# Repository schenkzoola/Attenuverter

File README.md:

<picture>
  <source media="(prefers-color-scheme: dark)" srcset="docs/images/logo-light.png">
  
</picture>

# Attenuverter

A 6HP Eurorack quad attenuverter from **Schenktronics**. Each of its four channels scales a signal by anywhere from ×1, through zero, to ×−1 (inverted), with a click at zero. Every input is normalled to +5 V, so with nothing plugged in, each channel is a manual offset from −5 V to +5 V.

## Features

- 6HP Eurorack, 20 mm deep. 16 mA on +12 V and 9 mA on −12 V.
- Four channels, each turning a signal down, off, or upside down
- Center-detent knobs, so zero is easy to find by feel
- Inputs normalled to +5 V: four manual offset voltages when nothing's plugged in
- Reverse-power protection on both rails

## Documentation

| Document | For | PDF |
|----------|-----|-----|
| [User Manual](docs/manual.md) | Using the module | [PDF](docs/pdf/attenuverter-manual.pdf) |
| [Assembly Guide](docs/assembly-guide.md) | Building the kit | [PDF](docs/pdf/attenuverter-assembly-guide.pdf) |
| [Bill of Materials](docs/BOM.md) ([CSV](docs/BOM.csv)) | Parts and sourcing | |

## Repository layout

```
Attenuverter/                 Main PCB (KiCad 5.1)
  Attenuverter.sch              Schematic
  Attenuverter.kicad_pcb        PCB layout
  Attenuverter.step             3D model
  Gerbers/, *Gerbers.zip        Fabrication files
  attenuverter BOM.xlsx         Original BOM spreadsheet
AttenuverterFaceplate/        Faceplate (KiCad 5.1, made as an aluminium PCB)
  *.dxf                         Panel outline and drill drawing
  *Gerbers/, *Gerbers.zip       Fabrication files
docs/                         Manual, assembly guide, BOM, images
  drawings/                     Scripts that generate the drawings
  pdf/                          PDF versions and their build settings
```

## Fabrication

| Board | Size | Layers | Thickness | Notes |
|-------|------|--------|-----------|-------|
| Main PCB | 30 × 100 mm | 2 | 1.6 mm | Standard green is fine |
| Faceplate | 30 × 128.5 mm | 1 | 1.6 mm | Aluminium PCB, white solder mask, black silkscreen. Only the front copper layer is used, so FR4 works too. |

Upload the matching `*Gerbers.zip` to any common PCB fab.

## License

This hardware design and its documentation are licensed under [CC BY-NC-SA 4.0](https://creativecommons.org/licenses/by-nc-sa/4.0/). See [LICENSE](LICENSE).

The Schenktronics name and logo are trademarks of Nathan Schenk and are not covered by the CC BY-NC-SA 4.0 license.

## Links

- Tindie: <https://www.tindie.com/products/schenktronics/attenuverter/>
- ModularGrid: <https://modulargrid.net/e/schenktronics-attenuverter>
- Build video: <https://www.youtube.com/watch?v=QJxtZVHBpq0>
- Website: <https://schenktronics.com>

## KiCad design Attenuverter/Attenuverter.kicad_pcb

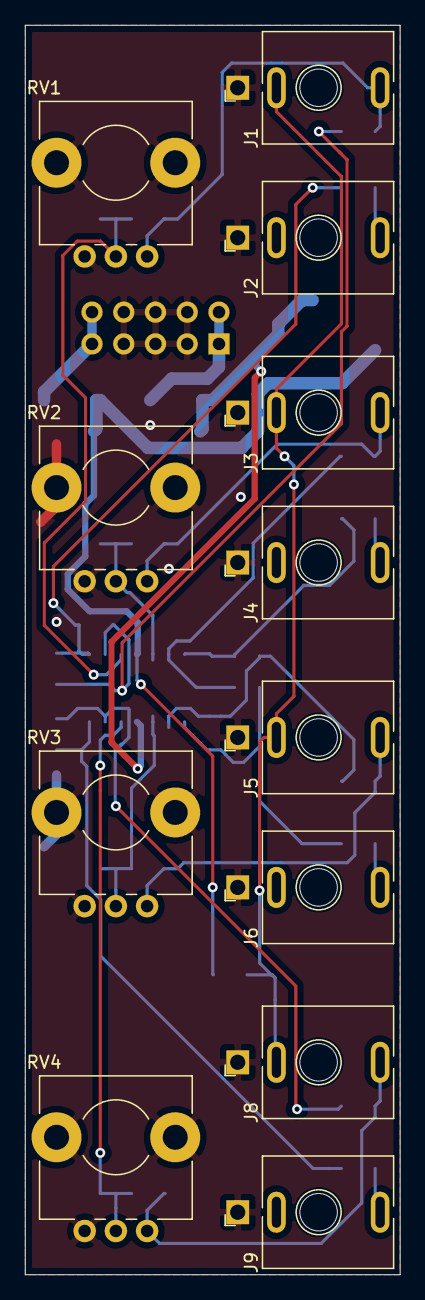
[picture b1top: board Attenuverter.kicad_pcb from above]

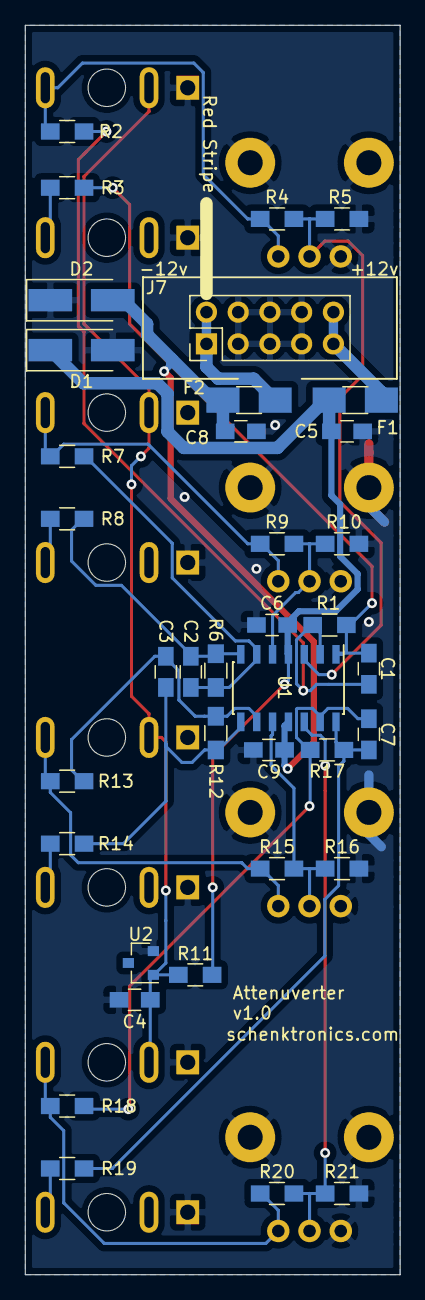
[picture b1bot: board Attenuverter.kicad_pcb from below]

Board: 2 copper layers, 30.0 x 100.0 mm, 49 parts (37 on the bottom side), 26 nets.

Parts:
C1, C2, C3, C7: 10pF; C_0805_HandSoldering
C4, C6, C9: 100nF; C_0805_HandSoldering
C5, C8: 10uF; C_0805_HandSoldering
D1, D2: D; D_SMA_Handsoldering
F1, F2: Polyfuse; Fuse_SMD1206_HandSoldering
J1, J2, J3, J4, J5, J6, J8, J9: AudioJack2_SwitchT; Jack_3.5mm_QingPu_WQP-PJ398SM_Vertical_CenterHole_OvalPads
J7: Conn_02x05_Odd_Even; PinHeader_2x05_P2.54mm_Vertical_Shrouded
R1, R2, R4, R5, R6, R7, R9, R10, R12, R13, R15, R16, R17, R18, R20, R21: 100k; R_0805_HandSoldering
R3, R8, R14, R19: 100; R_0805_HandSoldering
R11: 1k; R_0805_HandSoldering
RV1, RV2, RV3, RV4: 100k; Potentiometer_Alps_RK09L_Plated_Mount_Holes
U1: TL084; SOIC-14_3.9x8.7mm_Pitch1.27mm
U2: LM4040DBZ-5; SOT-23

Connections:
+5V: C4.1, J1.TN, J3.TN, J5.TN, J8.TN, R11.1, U2.1
+12V: C5.1, C6.1, D1.1, F1.2, R11.2, U1.4
-12V: C8.2, C9.2, D2.2, F2.2, U1.11
GND: C4.2, C5.2, C6.2, C8.1, C9.1, D1.2, D2.1, J1.S, J2.S, J3.S, J4.S, J5.S, J6.S, J7.3, J7.4, J7.5, J7.6, J7.7, J7.8, J8.S, J9.S, R5.1, R10.1, R16.1, R21.1, RV1.3, RV2.3, RV3.3, RV4.3, U2.2
unnamed: C1.1, R1.1, R3.2, U1.1
unnamed: C1.2, R1.2, R2.1, U1.2
unnamed: C2.1, R6.1, R8.2, U1.7
unnamed: C2.2, R6.2, R7.1, U1.6
unnamed: C3.1, R12.1, R14.2, U1.8
unnamed: C3.2, R12.2, R13.1, U1.9
unnamed: C7.1, R17.1, R19.2, U1.14
unnamed: C7.2, R17.2, R18.1, U1.13
unnamed: F1.1, J7.9, J7.10
unnamed: F2.1, J7.1, J7.2
unnamed: J1.T, R2.2, R4.2, RV1.1
unnamed: J2.T, R3.1
unnamed: J3.T, R7.2, R9.2, RV2.1
unnamed: J4.T, R8.1
unnamed: J5.T, R13.2, R15.2, RV3.1
unnamed: J6.T, R14.1
unnamed: J8.T, R18.2, R20.2, RV4.1
unnamed: J9.T, R19.1
unnamed: R4.1, R5.2, RV1.2, U1.3
unnamed: R9.1, R10.2, RV2.2, U1.5
unnamed: R15.1, R16.2, RV3.2, U1.10
unnamed: R20.1, R21.2, RV4.2, U1.12

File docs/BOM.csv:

Qty,Reference,Description,Manufacturer,Part Number,Link
1,U1,"Quad JFET op-amp, SOIC-14 (TL084 also works)",Texas Instruments,TL074CDR,https://www.ti.com/lit/ds/symlink/tl074.pdf
1,U2,"5.0V shunt voltage reference, SOT-23-3, cathode pin 1, anode pin 2 (or equivalent)",Microchip,LM4040DYM3-5.0-TR,https://www.ti.com/lit/ds/symlink/lm4040.pdf
16,"R1, R2, R4, R5, R6, R7, R9, R10, R12, R13, R15, R16, R17, R18, R20, R21","Resistor, 100k, 1%, 0805",Yageo,RC0805FR-07100KL,
4,"R3, R8, R14, R19","Resistor, 100 ohm, 1%, 0805",Yageo,RC0805FR-07100RL,
1,R11,"Resistor, 1k, 1%, 0805",Yageo,RC0805FR-071KL,
4,"C1, C2, C3, C7","Capacitor, 10pF, 50V, C0G/NP0, 0805",Yageo,CC0805JRNPO9BN100,
3,"C4, C6, C9","Capacitor, 100nF, 25V, X7R, 0805",AVX,08053C104KAT2A,
2,"C5, C8","Capacitor, 10uF, 25V, X5R, 0805",Taiyo Yuden,TMK212BBJ106KG-T,
2,"D1, D2","Diode, 1A, 300V, SMA",ON Semiconductor,MRA4003T3G,
2,"F1, F2","Resettable fuse (PTC), 200mA hold, 30V, 1206",Bel Fuse,0ZCJ0020FF2E,
1,J7,"Shrouded pin header, 2x5, 2.54mm, vertical",On Shore Technology,302-S101,
8,"J1-J6, J8, J9","3.5mm mono switched jack, vertical, with nut (CUI MJ-3507 also works, with a ground wire from its sleeve lug to the square pad)",QingPu,WQP-PJ398SM or WQP518MA,http://www.qingpu-electronics.com/en/products/WQP-PJ398SM-362.html
4,RV1-RV4,"Potentiometer, 100k linear, 9mm, center detent, bushingless, 25mm D shaft (or equivalent)",Bourns,PTV09A-4225F-B104,https://www.bourns.com/docs/Product-Datasheets/PTV09.pdf
4,,"Knob, fits 6mm D shaft (or equivalent)",Davies Molding,1221-J,
1,,"Main PCB, 30x100mm, 2-layer, 1.6mm",Schenktronics,Attenuverter v1.0,
1,,"Faceplate, 6HP, 1.6mm aluminium PCB",Schenktronics,Attenuverter Faceplate,
1,,"Eurorack power cable, 10-pin to 16-pin",,,

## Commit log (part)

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2019-11-25 Initial Commit
    Need to assign footprints and create PCB
2019-11-26 Assign footprints
    Layout Components
    Layout Board
    Add Gnd Pours
2019-11-26 Finish routing
2019-11-26 Generate gerbers and step
2019-11-28 Swap inverting and non inverting inputs. Generate gerbers
2019-11-28 Create faceplate pcb
2019-11-28 Finish faceplate
2020-04-18 Add titleblock details
2020-04-18 Add attenuverter BOM
    Remove -bak files
